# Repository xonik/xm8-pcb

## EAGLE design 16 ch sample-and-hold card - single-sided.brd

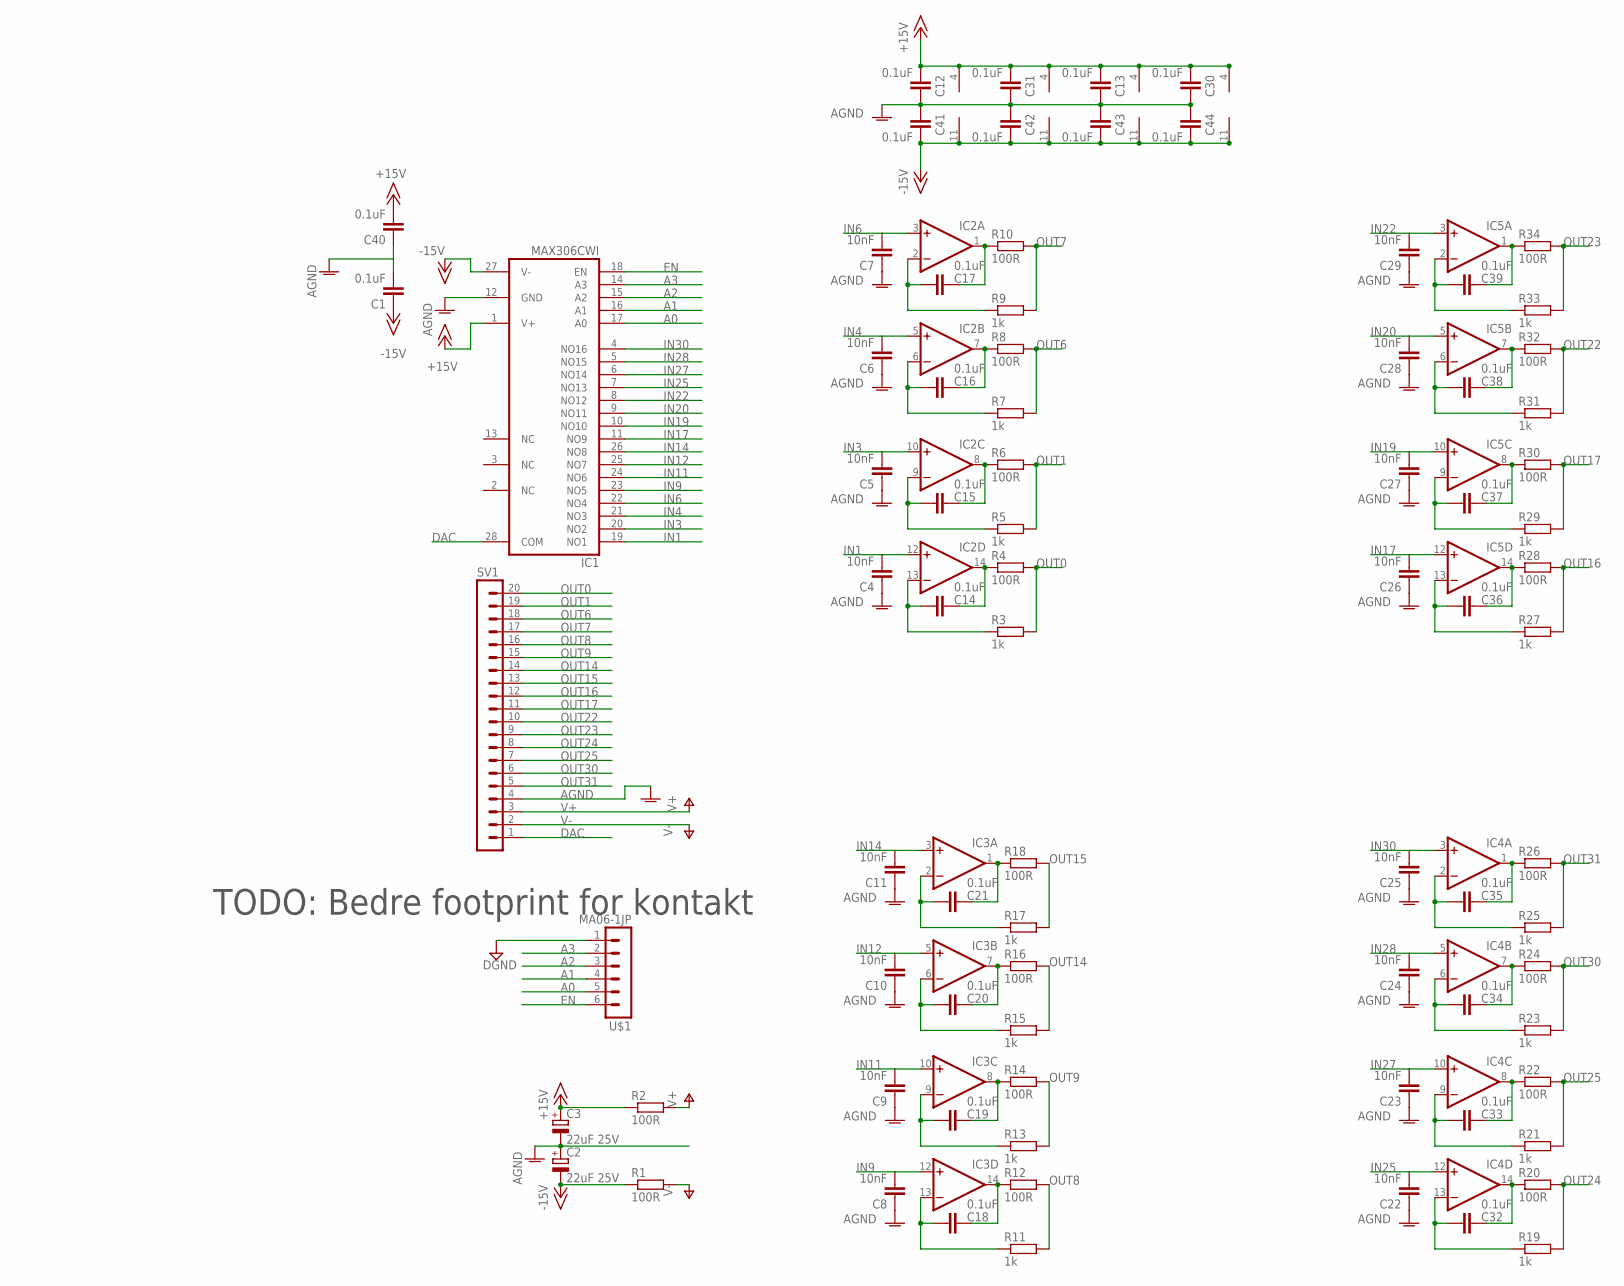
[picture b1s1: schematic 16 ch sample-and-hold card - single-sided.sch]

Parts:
C1, C12, C13, C14, C15, C16, C17, C18, C19, C20, C21, C30, C31, C32, C33, C34, C35, C36, C37, C38, C39, C40, C41, C42, C43, C44: 0.1uF; C0603
C2, C3: 22uF 25V; E2,5-5
C4, C5, C6, C7, C8, C9, C10, C11, C22, C23, C24, C25, C26, C27, C28, C29: 10nF; C1206
IC1: MAX306CWI; SO28L
IC2, IC3, IC4, IC5: TL074D; SO14
R1, R2: 100R; 0207/7
R3, R5, R7, R9, R11, R13, R15, R17, R19, R21, R23, R25, R27, R29, R31, R33: 1k; R0603
R4, R6, R8, R10, R12, R14, R16, R18, R20, R22, R24, R26, R28, R30, R32, R34: 100R; R0603
SV1: MA20-1JP; SIP-PIN20-1J
U$1: MA06-1JP; SIP-PIN06-1J

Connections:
+15V: C3.+, C12.1, C13.1, C30.1, C31.1, C40.2, IC1.1 (V+), IC2.4 (V+), IC3.4 (V+), IC4.4 (V+), IC5.4 (V+), R2.1
-15V: C1.1, C2.-, C41.2, C42.2, C43.2, C44.2, IC1.27 (V-), IC2.11 (V-), IC3.11 (V-), IC4.11 (V-), IC5.11 (V-), R1.1
A0: IC1.17 (A0), U$1.5
A1: IC1.16 (A1), U$1.4
A2: IC1.15 (A2), U$1.3
A3: IC1.14 (A3), U$1.2
AGND: C1.2, C2.+, C3.-, C4.1, C5.1, C6.1, C7.1, C8.1, C9.1, C10.1, C11.1, C12.2, C13.2, C22.1, C23.1, C24.1, C25.1, C26.1, C27.1, C28.1, C29.1, C30.2, C31.2, C40.1, C41.1, C42.1, C43.1, C44.1, IC1.12 (GND), SV1.4
DAC: IC1.28 (COM), SV1.1
DGND: U$1.1
EN: IC1.18 (EN), U$1.6
IN1: C4.2, IC1.19 (NO1), IC2.12 (+IN)
IN3: C5.2, IC1.20 (NO2), IC2.10 (+IN)
IN4: C6.2, IC1.21 (NO3), IC2.5 (+IN)
IN6: C7.2, IC1.22 (NO4), IC2.3 (+IN)
IN9: C8.2, IC1.23 (NO5), IC3.12 (+IN)
IN11: C9.2, IC1.24 (NO6), IC3.10 (+IN)
IN12: C10.2, IC1.25 (NO7), IC3.5 (+IN)
IN14: C11.2, IC1.26 (NO8), IC3.3 (+IN)
IN17: C26.2, IC1.11 (NO9), IC5.12 (+IN)
IN19: C27.2, IC1.10 (NO10), IC5.10 (+IN)
IN20: C28.2, IC1.9 (NO11), IC5.5 (+IN)
IN22: C29.2, IC1.8 (NO12), IC5.3 (+IN)
IN25: C22.2, IC1.7 (NO13), IC4.12 (+IN)
IN27: C23.2, IC1.6 (NO14), IC4.10 (+IN)
IN28: C24.2, IC1.5 (NO15), IC4.5 (+IN)
IN30: C25.2, IC1.4 (NO16), IC4.3 (+IN)
unnamed: C17.2, IC2.2 (-IN), R9.1
unnamed: C17.1, IC2.1 (OUT), R10.1
unnamed: C16.1, IC2.7 (OUT), R8.1
unnamed: C15.1, IC2.8 (OUT), R6.1
unnamed: C16.2, IC2.6 (-IN), R7.1
unnamed: C14.1, IC2.14 (OUT), R4.1
unnamed: C15.2, IC2.9 (-IN), R5.1
unnamed: C14.2, IC2.13 (-IN), R3.1
unnamed: C21.1, IC3.1 (OUT), R18.1
unnamed: C21.2, IC3.2 (-IN), R17.1
unnamed: C20.1, IC3.7 (OUT), R16.1
unnamed: C20.2, IC3.6 (-IN), R15.1
unnamed: C19.1, IC3.8 (OUT), R14.1
unnamed: C18.1, IC3.14 (OUT), R12.1
unnamed: C19.2, IC3.9 (-IN), R13.1
unnamed: C18.2, IC3.13 (-IN), R11.1
unnamed: C39.1, IC5.1 (OUT), R34.1
unnamed: C39.2, IC5.2 (-IN), R33.1
unnamed: C38.1, IC5.7 (OUT), R32.1
unnamed: C38.2, IC5.6 (-IN), R31.1
unnamed: C37.1, IC5.8 (OUT), R30.1
unnamed: C36.1, IC5.14 (OUT), R28.1
unnamed: C37.2, IC5.9 (-IN), R29.1
unnamed: C36.2, IC5.13 (-IN), R27.1
unnamed: C35.1, IC4.1 (OUT), R26.1
unnamed: C35.2, IC4.2 (-IN), R25.1
unnamed: C34.1, IC4.7 (OUT), R24.1
unnamed: C34.2, IC4.6 (-IN), R23.1
unnamed: C33.1, IC4.8 (OUT), R22.1
unnamed: C32.1, IC4.14 (OUT), R20.1
unnamed: C33.2, IC4.9 (-IN), R21.1
unnamed: C32.2, IC4.13 (-IN), R19.1
OUT0: R3.2, R4.2, SV1.20
OUT1: R5.2, R6.2, SV1.19
OUT6: R7.2, R8.2, SV1.18
OUT7: R9.2, R10.2, SV1.17
OUT8: R11.2, R12.2, SV1.16
OUT9: R13.2, R14.2, SV1.15
OUT14: R15.2, R16.2, SV1.14
OUT15: R17.2, R18.2, SV1.13
OUT16: R27.2, R28.2, SV1.12
OUT17: R29.2, R30.2, SV1.11
OUT22: R31.2, R32.2, SV1.10
OUT23: R33.2, R34.2, SV1.9
OUT24: R19.2, R20.2, SV1.8
OUT25: R21.2, R22.2, SV1.7
OUT30: R23.2, R24.2, SV1.6
OUT31: R25.2, R26.2, SV1.5
V+: R2.2, SV1.3
V-: R1.2, SV1.2

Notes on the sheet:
TODO: Bedre footprint for kontakt

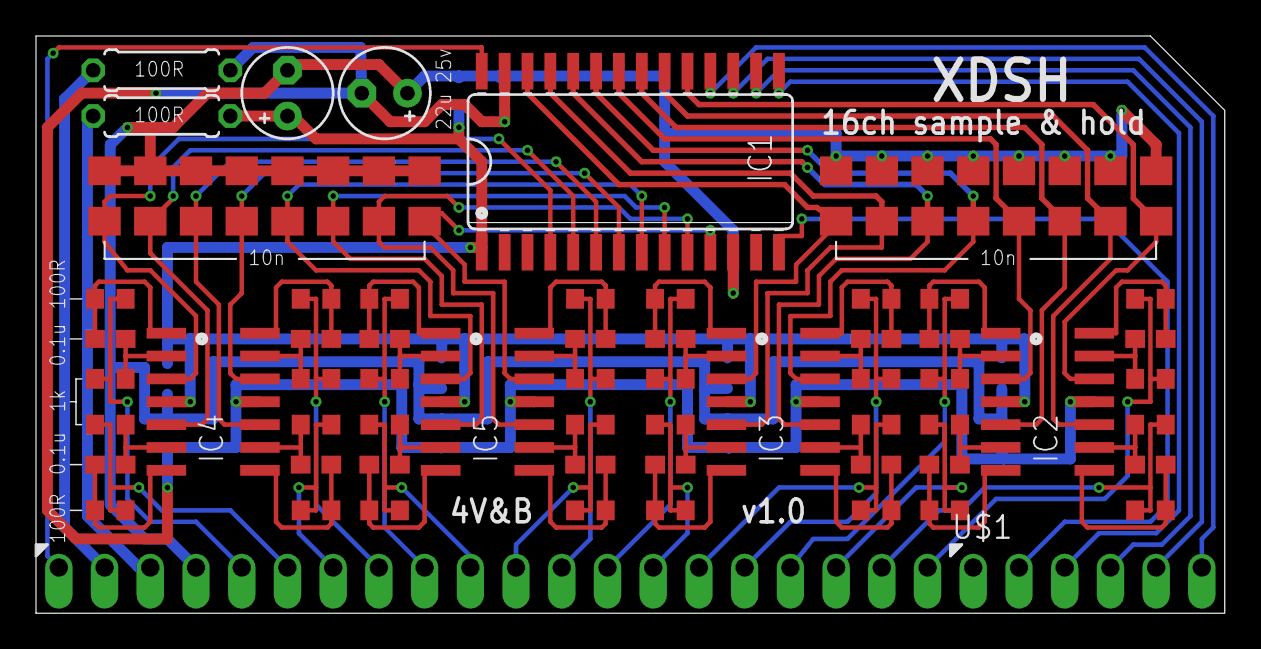
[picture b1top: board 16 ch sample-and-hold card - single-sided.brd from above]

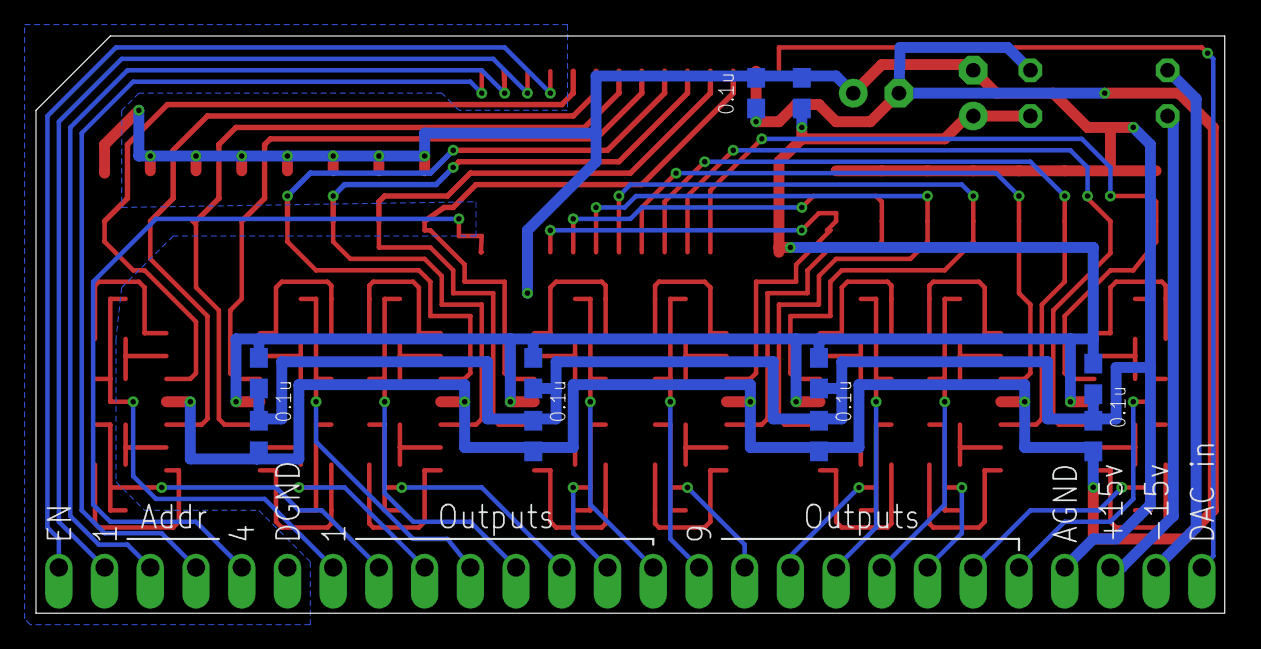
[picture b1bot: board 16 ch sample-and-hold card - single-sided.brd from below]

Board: 2 copper layers, 66.0 x 32.1 mm, 85 parts (10 on the bottom side), 75 nets.

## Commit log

2017-09-08 Initial commit, moved contents from google drive
2018-07-22 Reworked resistor and electrolytic caps placement to tap power AFTER caps for better noise filtering
2018-07-22 Single sided board routed, gonna try moving power lines
2018-07-22 Almost finished, trying to reroute address lines
2018-07-22 Rerouted address lines
2018-07-22 Tweaked cap positions
2018-07-22 Changed pin labels after moving address pins
2018-07-23 Last commit before moving multiplexer to separate repo
2018-07-23 Moved multiplexer to separate repo
2018-07-23 Moved sample and hold circuits to dac-multiplexer-pcb
2020-02-26 Added git ignore
